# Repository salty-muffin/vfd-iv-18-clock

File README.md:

# vfd-iv-18-clock

A clock build around a iv-18 vacuum flourecent display

all libraries in the lib directory must be copied to the lib directory of the raspberry pi pico (all python files in the subdirectories should be copied directly)

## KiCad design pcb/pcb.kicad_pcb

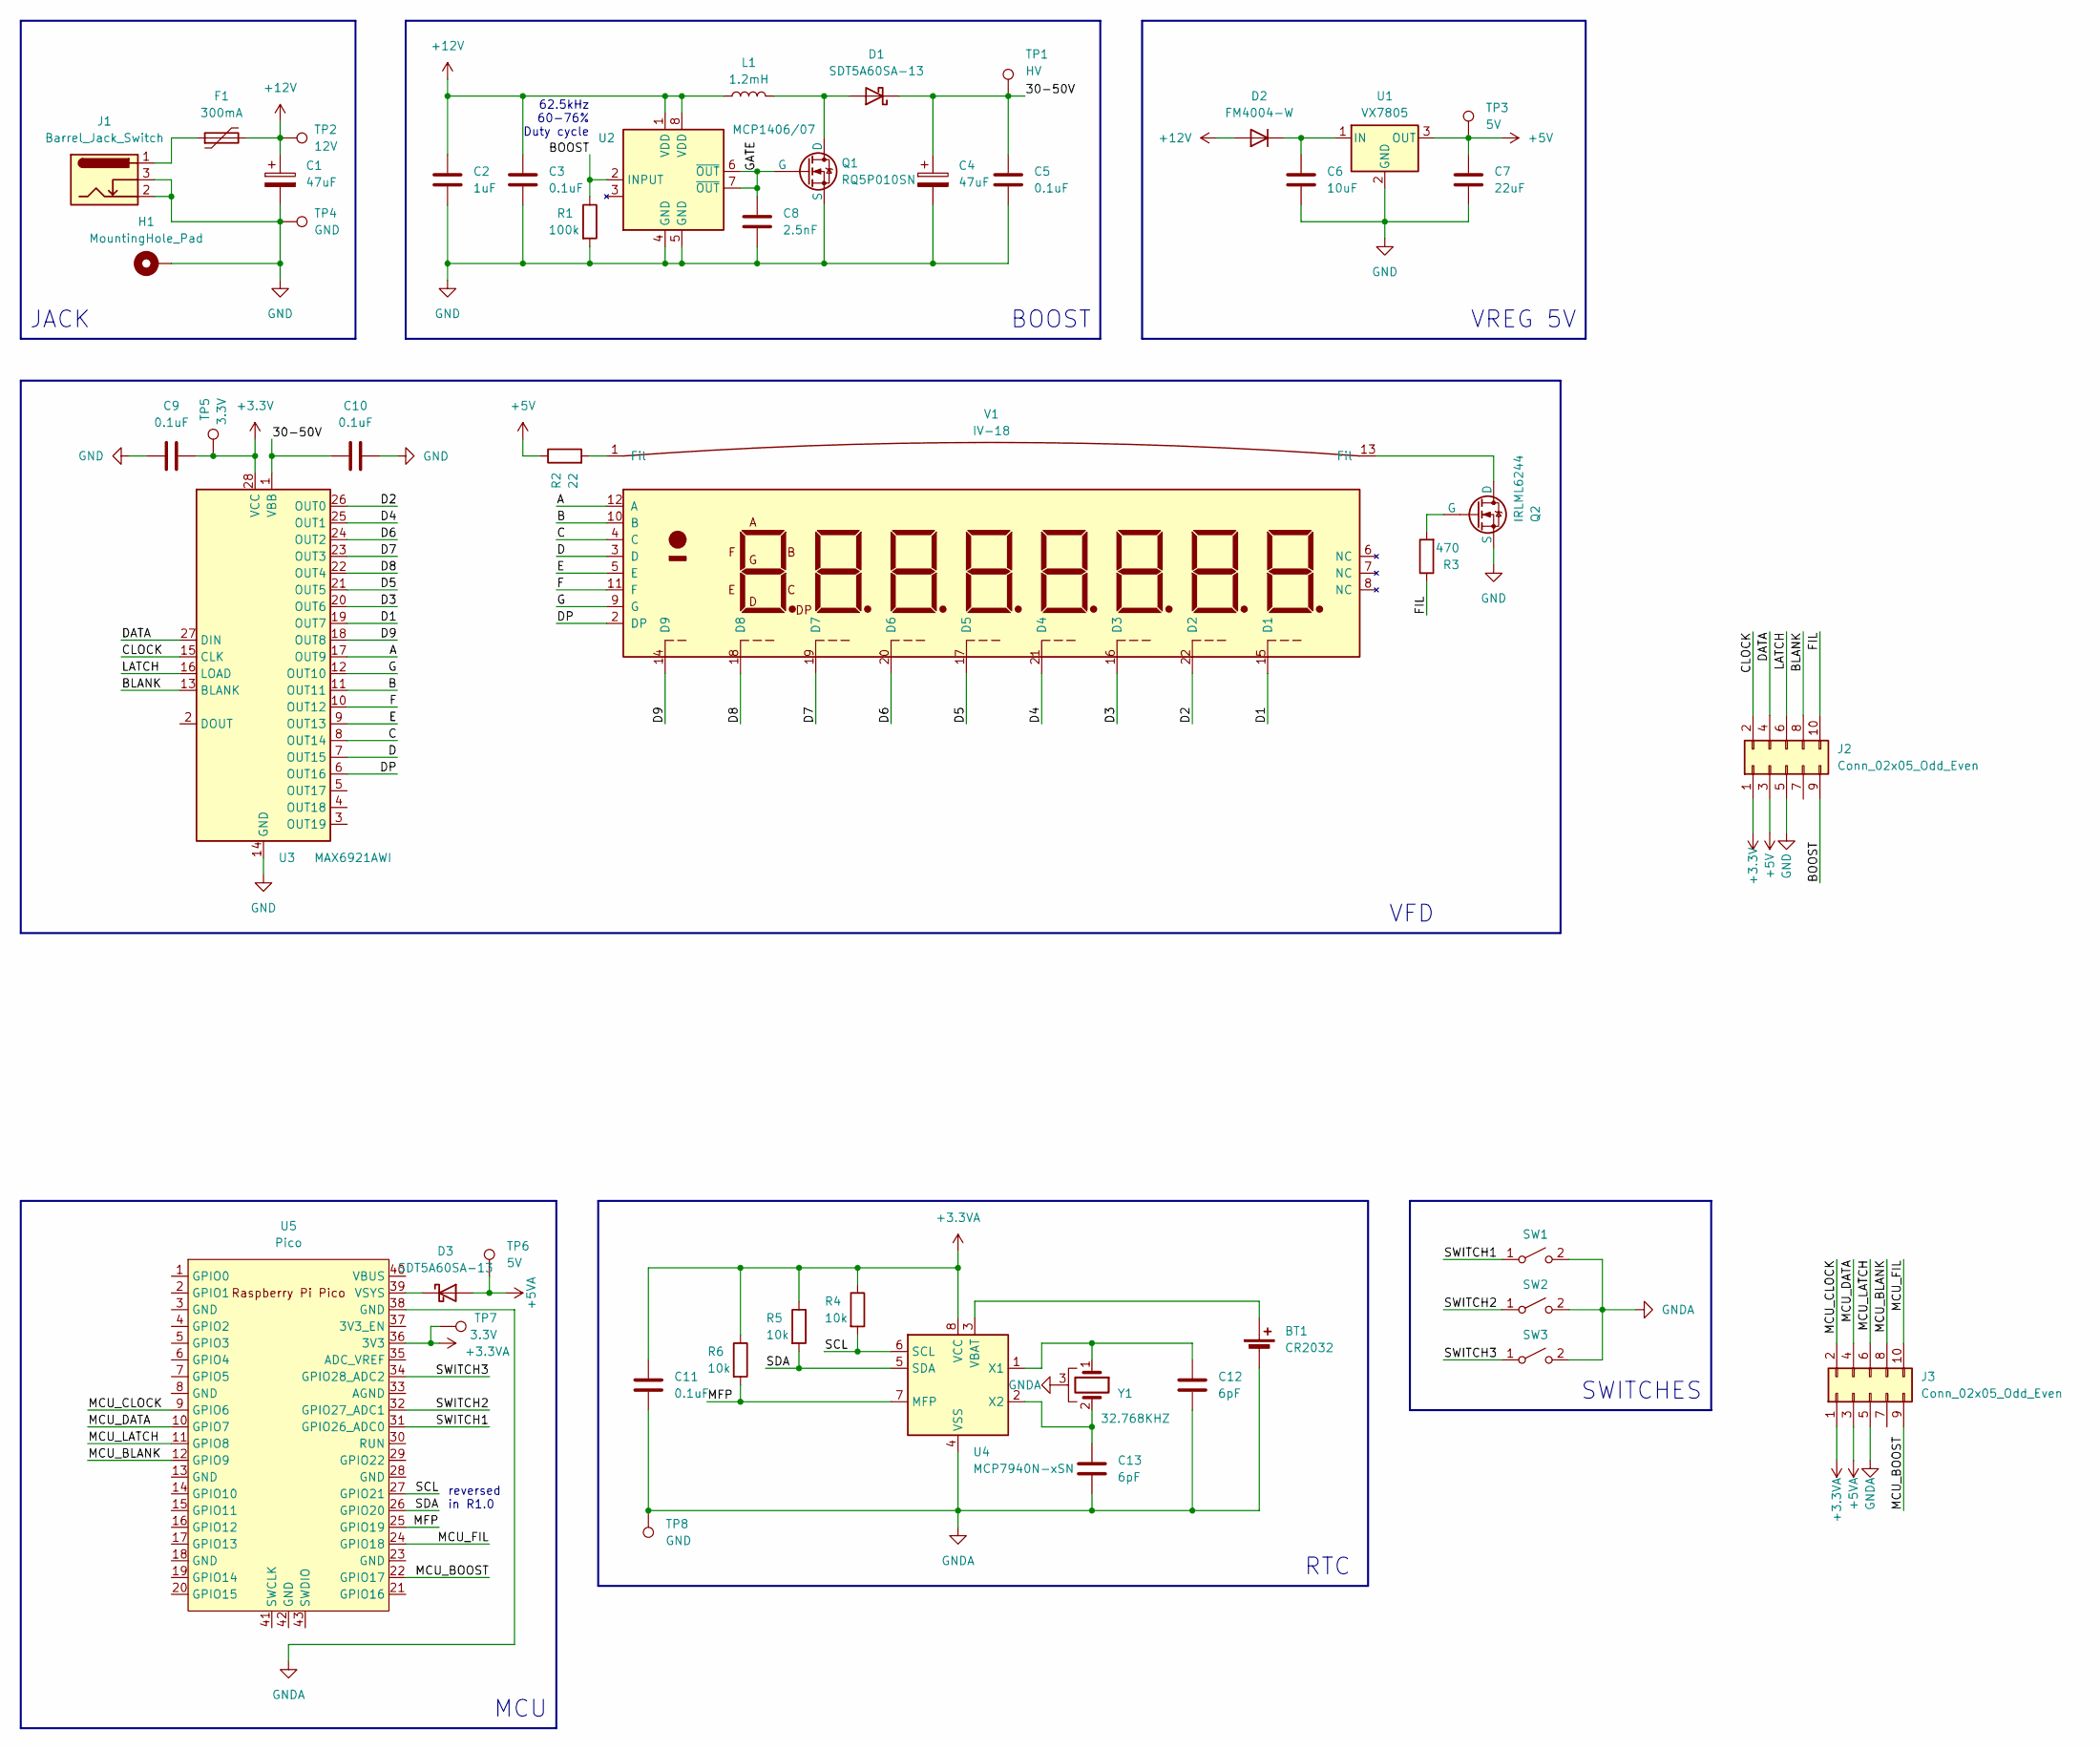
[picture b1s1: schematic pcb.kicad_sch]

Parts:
BT1: CR2032; BatteryHolder_Keystone_3002_1x2032
C1, C4: 47uF; CP_Radial_D8.0mm_P3.50mm
C2: 1uF; C_Rect_L7.2mm_W5.5mm_P5.00mm_FKS2_FKP2_MKS2_MKP2
C3, C5, C9, C10, C11: 0.1uF; C_1206_3216Metric_Pad1.33x1.80mm_HandSolder
C6: 10uF; C_1206_3216Metric_Pad1.33x1.80mm_HandSolder
C7: 22uF; C_1206_3216Metric_Pad1.33x1.80mm_HandSolder
C8: 2.5nF; C_1206_3216Metric_Pad1.33x1.80mm_HandSolder
C12, C13: 6pF; C_1206_3216Metric_Pad1.33x1.80mm_HandSolder
D1, D3: SDT5A60SA-13; D_SMA_Handsoldering
D2: FM4004-W; D_SMA_Handsoldering
F1: 300mA; Fuse_1812_4532Metric_Pad1.30x3.40mm_HandSolder
H1: MountingHole_Pad; MountingHole_3.2mm_M3_DIN965_Pad
J1: Barrel_Jack_Switch; BarrelJack_Wuerth_6941xx301002
J2, J3: Conn_02x05_Odd_Even; PinSocket_2x05_P2.54mm_Vertical
L1: 1.2mH; L_Radial_D9.5mm_P5.00mm_Fastron_07HVP
Q1: RQ5P010SN; SOT-23_Handsoldering
Q2: IRLML6244; SOT-23_Handsoldering
R1: 100k; R_1206_3216Metric_Pad1.30x1.75mm_HandSolder
R2: 22; R_1206_3216Metric_Pad1.30x1.75mm_HandSolder
R3: 470; R_1206_3216Metric_Pad1.30x1.75mm_HandSolder
R4, R5, R6: 10k; R_1206_3216Metric_Pad1.30x1.75mm_HandSolder
SW1, SW2, SW3: SW_SPST; SW_Tactile_SPST_Angled_PTS645Vx83-2LFS
TP1: HV; TestPoint_THTPad_D1.5mm_Drill0.7mm
TP2: 12V; TestPoint_THTPad_D1.5mm_Drill0.7mm
TP3, TP6: 5V; TestPoint_THTPad_D1.5mm_Drill0.7mm
TP4, TP8: GND; TestPoint_THTPad_D1.5mm_Drill0.7mm
TP5, TP7: 3.3V; TestPoint_THTPad_D1.5mm_Drill0.7mm
U1: VX7805
U2: MCP1406/07; SOIC-8_3.9x4.9mm_P1.27mm
U3: MAX6921AWI; SOIC-28W_7.5x17.9mm_P1.27mm
U4: MCP7940N-xSN; SOIC-8_3.9x4.9mm_P1.27mm
U5: Pico; RPi_Pico_SMD
V1: IV-18
Y1: 32.768KHZ; Crystal_DS26_D2.0mm_L6.0mm_Horizontal_Grounded_SMT

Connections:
+3.3V: C9.2, J2.1, TP5.1, U3.28 (VCC)
+3.3VA: C11.1, J3.1, R4.1, R5.1, R6.1, TP7.1, U4.8 (VCC), U5.36 (3V3)
+5V: C7.1, J2.3, R2.1, TP3.1, U1.3 (OUT)
+5VA: D3.2 (A), J3.3, TP6.1
+12V: C1.1, C2.1, C3.1, D2.2 (A), F1.2, L1.1, TP2.1, U2.1 (VDD), U2.8 (VDD)
/30-50V: C4.1, C5.1, C10.1, D1.1 (K), TP1.1, U3.1 (VBB)
/A: U3.17 (OUT9), V1.12 (A)
/B: U3.11 (OUT11), V1.10 (B)
/BLANK: J2.8, U3.13 (BLANK)
/BOOST: J2.9, R1.1, U2.2 (INPUT)
/C: U3.8 (OUT14), V1.4 (C)
/CLOCK: J2.2, U3.15 (CLK)
/D: U3.7 (OUT15), V1.3 (D)
/D1: U3.19 (OUT7), V1.15 (D1)
/D2: U3.26 (OUT0), V1.22 (D2)
/D3: U3.20 (OUT6), V1.16 (D3)
/D4: U3.25 (OUT1), V1.21 (D4)
/D5: U3.21 (OUT5), V1.17 (D5)
/D6: U3.24 (OUT2), V1.20 (D6)
/D7: U3.23 (OUT3), V1.19 (D7)
/D8: U3.22 (OUT4), V1.18 (D8)
/D9: U3.18 (OUT8), V1.14 (D9)
/DATA: J2.4, U3.27 (DIN)
/DP: U3.6 (OUT16), V1.2 (DP)
/E: U3.9 (OUT13), V1.5 (E)
/F: U3.10 (OUT12), V1.11 (F)
/FIL: J2.10, R3.1
/G: U3.12 (OUT10), V1.9 (G)
/GATE: C8.1, Q1.1 (G), U2.6 (~OUT), U2.7 (~OUT)
/LATCH: J2.6, U3.16 (LOAD)
/MCU_BLANK: J3.8, U5.12 (GPIO9)
/MCU_BOOST: J3.9, U5.22 (GPIO17)
/MCU_CLOCK: J3.2, U5.9 (GPIO6)
/MCU_DATA: J3.4, U5.10 (GPIO7)
/MCU_FIL: J3.10, U5.24 (GPIO18)
/MCU_LATCH: J3.6, U5.11 (GPIO8)
/MFP: R6.2, U4.7 (MFP), U5.25 (GPIO19)
/SCL: R4.2, U4.6 (SCL), U5.27 (GPIO21)
/SDA: R5.2, U4.5 (SDA), U5.26 (GPIO20)
/SWITCH1: SW1.1 (A), U5.31 (GPIO26_ADC0)
/SWITCH2: SW2.1 (A), U5.32 (GPIO27_ADC1)
/SWITCH3: SW3.1 (A), U5.34 (GPIO28_ADC2)
GND: C1.2, C2.2, C3.2, C4.2, C5.2, C6.2, C7.2, C8.2, C9.1, C10.2, H1.1, J1.2, J1.3, J2.5, Q1.2 (S), Q2.2 (S), R1.2, TP4.1, U1.2 (GND), U2.4 (GND), U2.5 (GND), U3.14 (GND)
GNDA: BT1.2 (-), C11.2, C12.2, C13.2, J3.5, SW1.2 (B), SW2.2 (B), SW3.2 (B), TP8.1, U4.4 (VSS), U5.38 (GND), Y1.3
unnamed: BT1.1 (+), U4.3 (VBAT)
unnamed: D1.2 (A), L1.2, Q1.3 (D)
unnamed: C6.1, D2.1 (K), U1.1 (IN)
unnamed: D3.1 (K), U5.39 (VSYS)
unnamed: F1.1, J1.1
unnamed: Q2.3 (D), V1.13 (Fil)
unnamed: Q2.1 (G), R3.2
unnamed: R2.2, V1.1 (Fil)
unnamed: C12.1, U4.1 (X1), Y1.1
unnamed: C13.1, U4.2 (X2), Y1.2

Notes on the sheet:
MCU
SWITCHES
62.5kHz 60-76% Duty cycle
reversed in R1.0
JACK
VFD
BOOST
VREG 5V
RTC

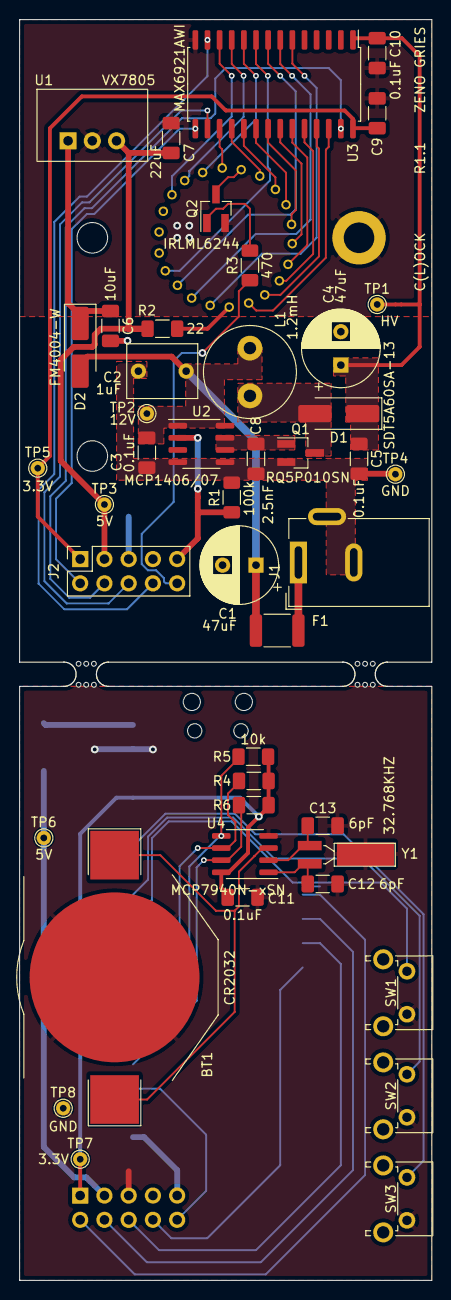
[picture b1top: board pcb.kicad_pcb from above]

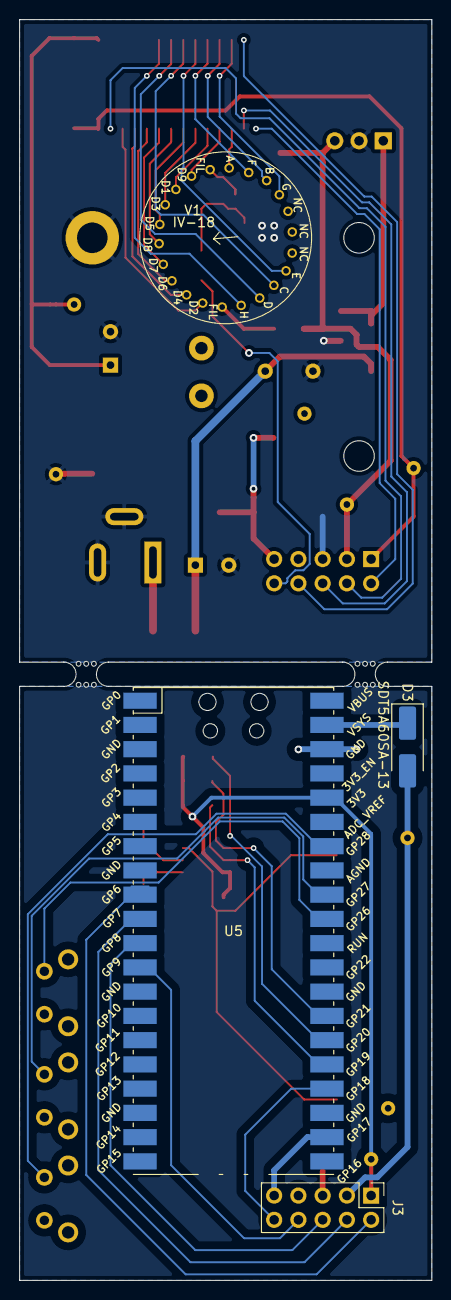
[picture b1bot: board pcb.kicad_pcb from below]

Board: 2 copper layers, 43.2 x 132.1 mm, 51 parts (3 on the bottom side), 54 nets.

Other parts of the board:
mouse-bite-2.54mm-slot, mouse-bite-2.54mm-slot#2: VAL**; mouse-bite-2.54mm-slot

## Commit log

2023-10-06 added pcb
2023-10-11 finished routing
2023-10-12 finished pcb
2023-10-12 fixed some traces
2023-10-14 rotated display
2023-10-14 added gitignore
2023-10-14 added credentials
2023-10-14 minor fixes
2023-10-14 added bom
2023-10-15 new pcb design
2023-10-16 small fixes
2023-10-16 decreased costs
2023-11-15 added info for boost converter signal
2023-11-16 added first scripts
2023-11-16 added rtc submodule
2023-11-16 started on a debouncer
2023-11-17 added mocj time and date display
2023-11-17 started on the mode selector
2023-11-20 added shift register code
2023-11-23 updated pcb to R1.1
2023-11-23 added display logic
2023-11-24 first working version
2023-11-25 finished main clock script
2023-11-25 added resettable fuse
2023-11-25 fixed display not blanking
2023-11-25 removed obsolete test script
2023-11-26 fixed type error
2023-11-26 added micropico
2023-11-26 exchanged lm7805 for vx7805
2023-11-26 removed obsolte lines
2023-11-26 implemented multithreading
2023-11-26 changed comments
2023-11-26 implemented better timing logic
2023-11-26 removed obsolete imports
2023-11-26 safer exception handling
2023-11-26 removed obsolete variables
2023-11-26 updated mcp7940
2023-11-26 validates the date on start
2023-11-26 enabled battery backend consistently
2023-11-26 removed redundancies
2023-11-26 increased frequency
2023-11-26 reintroduced mousebites
2023-11-27 added test script for calibration
2023-11-28 finished calibration script
2023-12-03 removed obsolete code
2023-12-03 added auto calibration script
2023-12-14 adjusted trimming for 6pF caps
2024-01-01 added svg for cutting
2024-01-04 added new cuts
